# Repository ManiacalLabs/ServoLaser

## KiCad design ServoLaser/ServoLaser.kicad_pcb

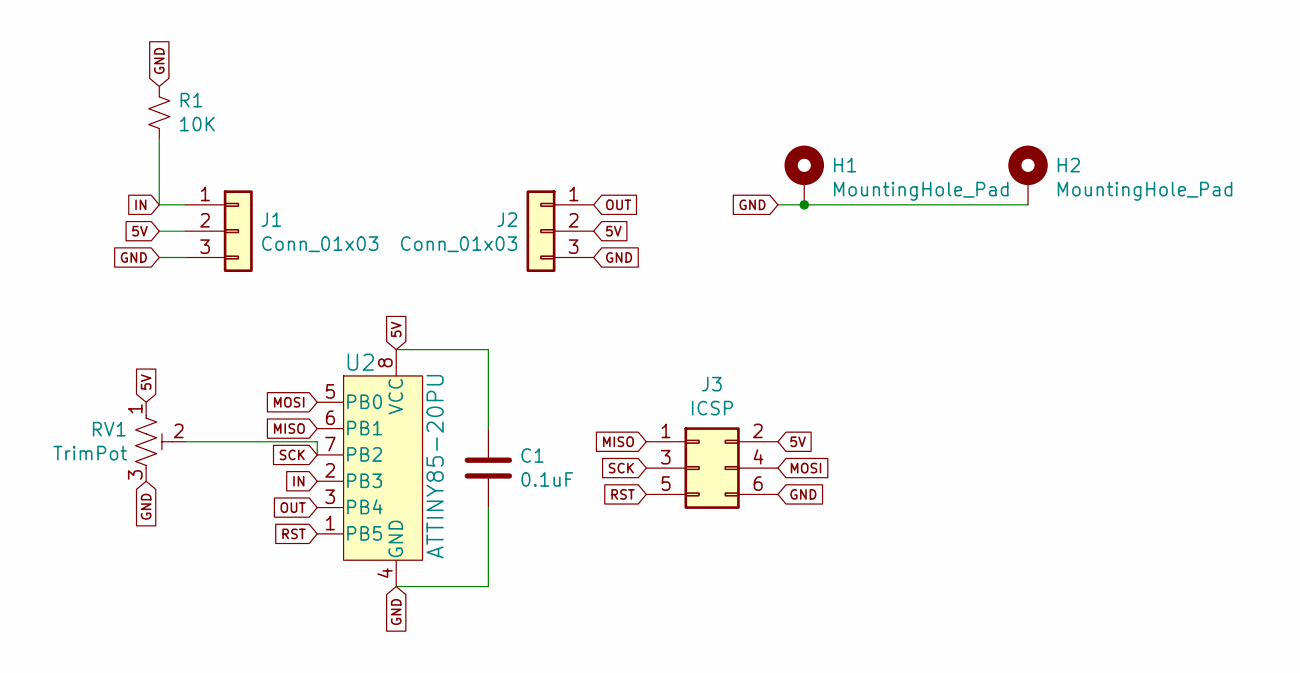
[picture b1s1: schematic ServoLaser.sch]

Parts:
C1: 0.1uF; C_Disc_D3.0mm_W1.6mm_P2.50mm
H1, H2: MountingHole_Pad; MountingHole_3.2mm_M3_Pad
J1: Conn_01x03; TerminalBlock_Phoenix_MPT-0,5-3-2.54_1x03_P2.54mm_Horizontal
J2: Conn_01x03; PinHeader_1x03_P2.54mm_Vertical
J3: ICSP; PinHeader_2x03_P2.54mm_Vertical
R1: 10K; R_Axial_DIN0204_L3.6mm_D1.6mm_P5.08mm_Horizontal
RV1: TrimPot; Potentiometer_Vishay_T73YP_Vertical
U2: ATTINY85-20PU; DIP-8_W7.62mm; MPN ATTINY85-20PU; Digi-Key_PN ATTINY85-20PU-ND

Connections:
5V: C1.1, J1.2, J2.2, J3.2, RV1.1, U2.8 (VCC)
GND: C1.2, H1.1, H2.1, J1.3, J2.3, J3.6, R1.1, RV1.3, U2.4 (GND)
IN: J1.1, R1.2, U2.2 (PB3)
MISO: J3.1, U2.6 (PB1)
MOSI: J3.4, U2.5 (PB0)
OUT: J2.1, U2.3 (PB4)
RST: J3.5, U2.1 (PB5)
SCK: J3.3, RV1.2, U2.7 (PB2)

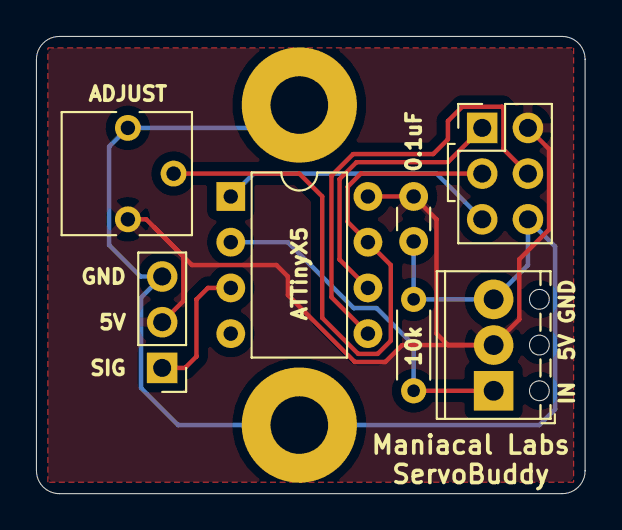
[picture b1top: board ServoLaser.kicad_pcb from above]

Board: 2 copper layers, 30.5 x 25.4 mm, 9 parts (0 on the bottom side), 8 nets.

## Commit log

2020-08-22 Add note about ATTinyCore
2020-08-23 Adding CAD models
2020-09-15 change name
